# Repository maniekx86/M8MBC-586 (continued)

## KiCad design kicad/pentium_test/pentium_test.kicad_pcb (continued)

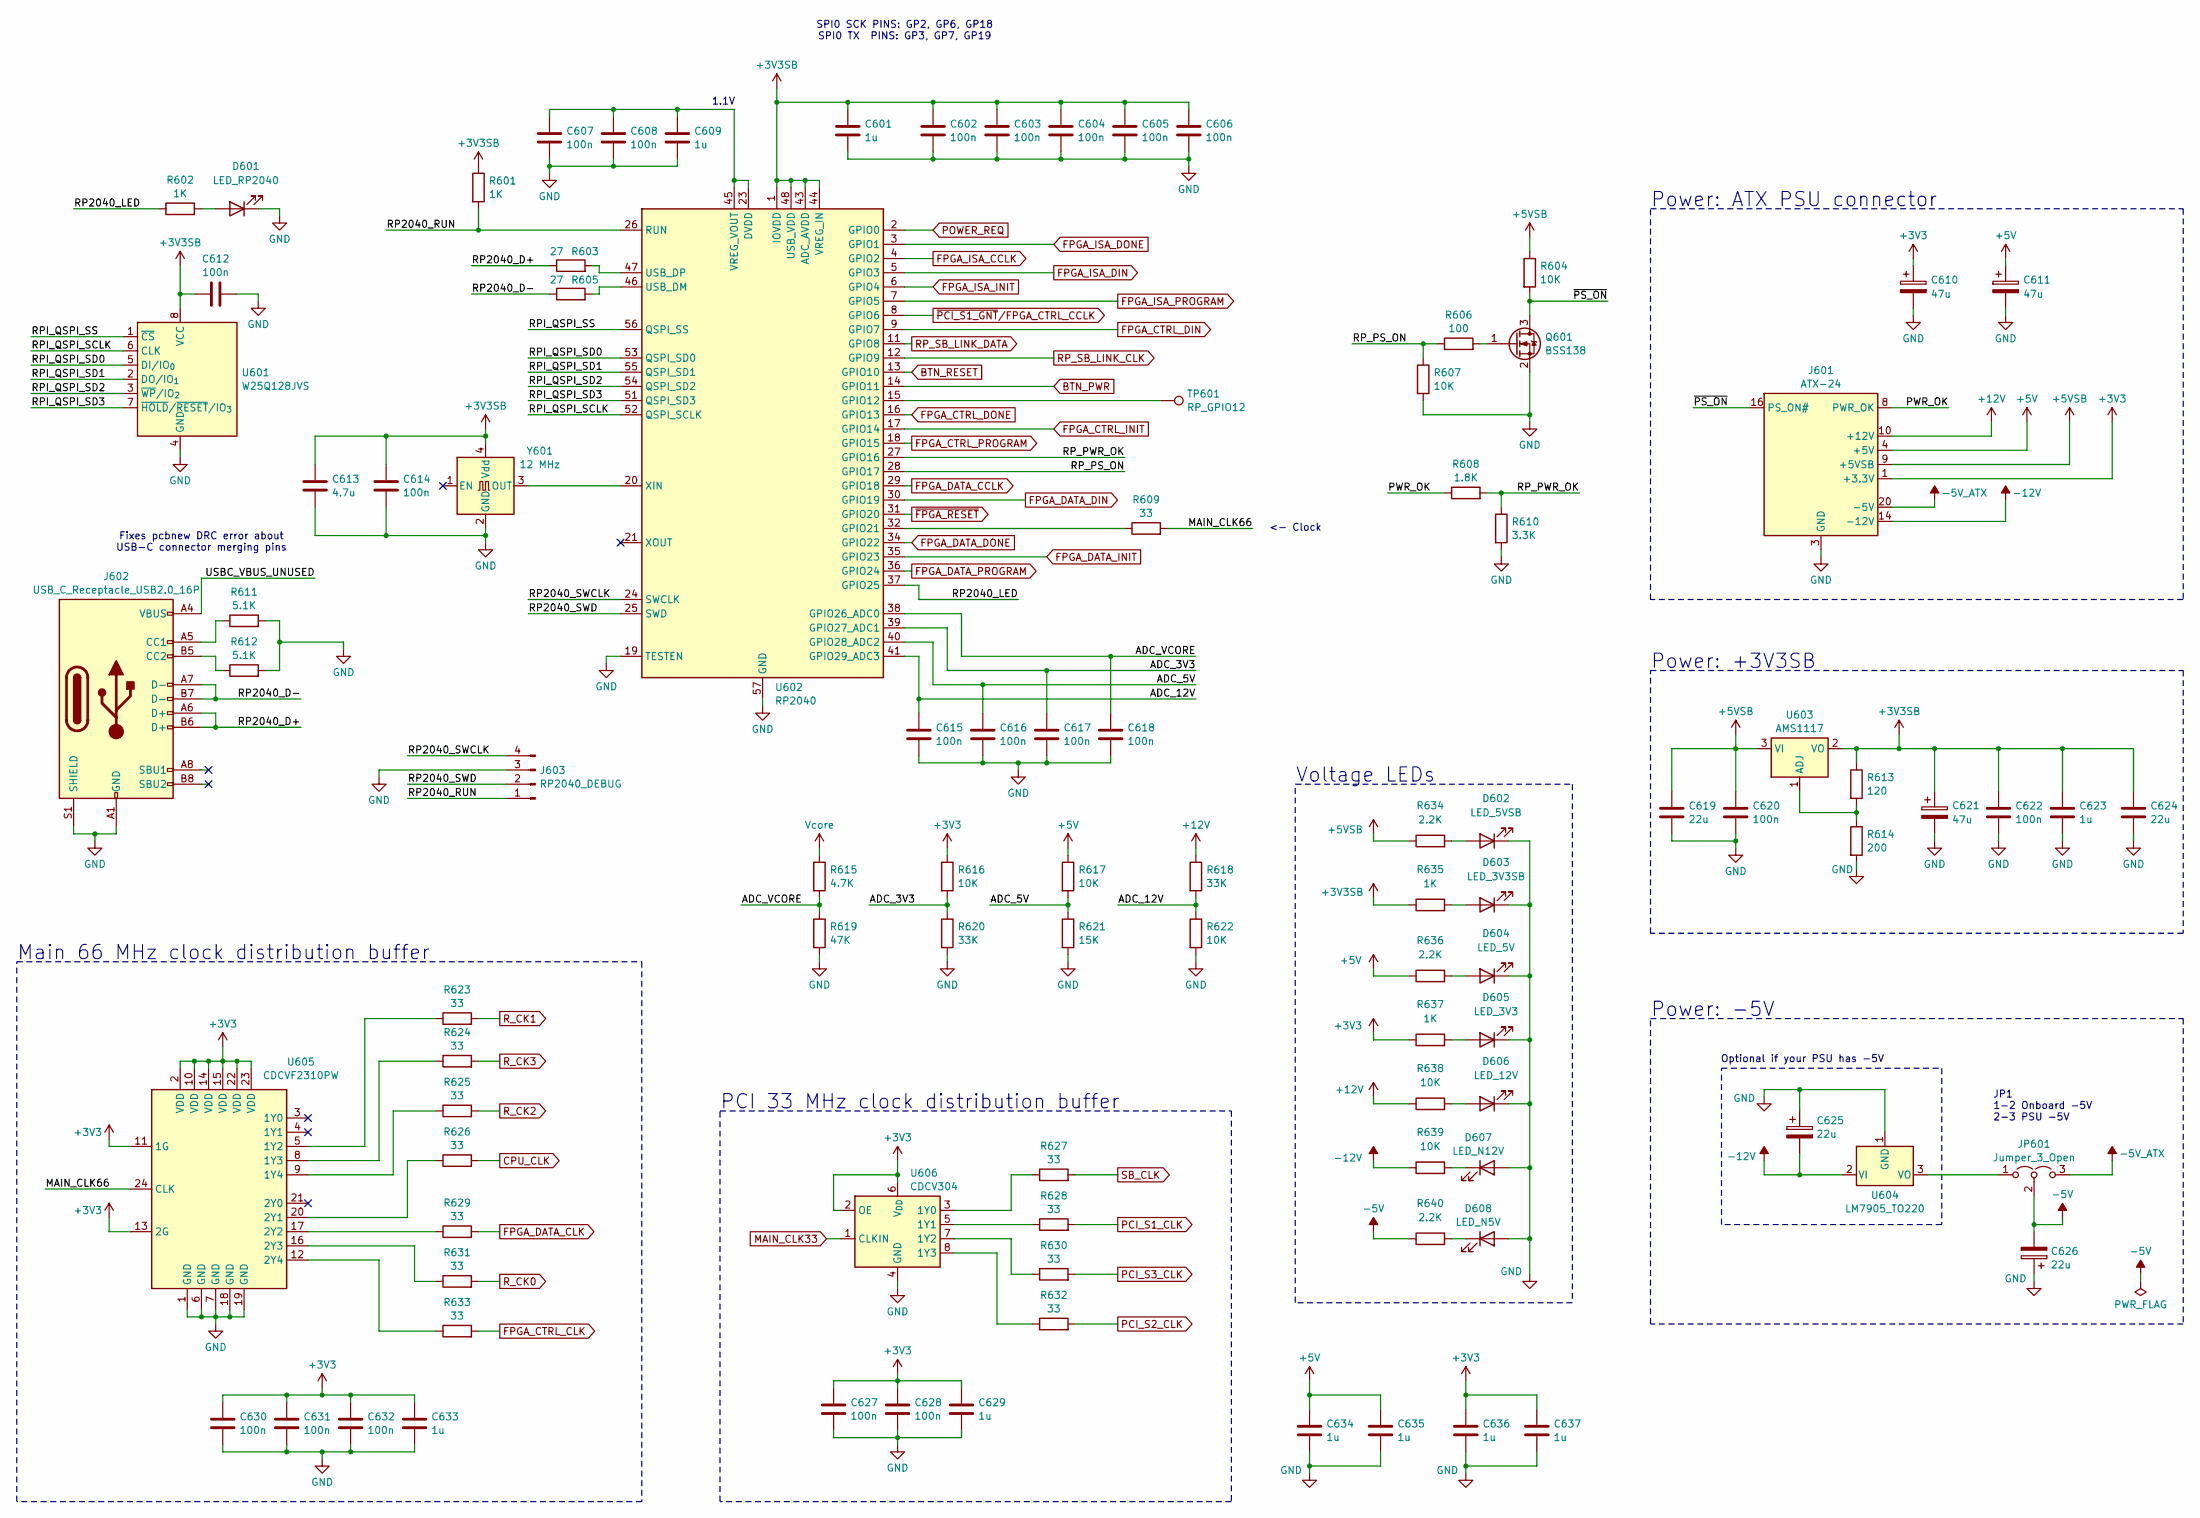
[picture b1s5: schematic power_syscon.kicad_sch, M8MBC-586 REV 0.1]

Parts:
C601, C609, C623, C629, C633, C634, C635, C636, C637: 1u; C_0805_2012Metric
C602, C603, C604, C605, C606, C607, C608, C612, C614, C615, C616, C617, C618, C620, C622, C627, C628, C630, C631, C632: 100n; C_0603_1608Metric
C610, C611, C621: 47u; CP_Radial_D5.0mm_P2.50mm
C613: 4.7u; C_0603_1608Metric
C619, C624: 22u; C_1206_3216Metric
C625, C626: 22u; CP_Radial_D5.0mm_P2.50mm
D601: LED_RP2040; LED_0603_1608Metric
D602: LED_5VSB; LED_0603_1608Metric
D603: LED_3V3SB; LED_0603_1608Metric
D604: LED_5V; LED_0603_1608Metric
D605: LED_3V3; LED_0603_1608Metric
D606: LED_12V; LED_0603_1608Metric
D607: LED_N12V; LED_0603_1608Metric
D608: LED_N5V; LED_0603_1608Metric
J601: ATX-24; Molex_Mini-Fit_Jr_5566-24A2_2x12_P4.20mm_Vertical
J602: USB_C_Receptacle_USB2.0_16P; USB_C_Receptacle_HRO_TYPE-C-31-M-12
J603: RP2040_DEBUG; PinHeader_1x04_P2.54mm_Vertical
JP601: Jumper_3_Open; PinHeader_1x03_P2.54mm_Vertical
Q601: BSS138; SOT-23
R601, R602, R635, R637: 1K; R_0603_1608Metric
R603, R605: 27; R_0603_1608Metric
R604, R607, R616, R617, R622, R638, R639: 10K; R_0603_1608Metric
R606: 100; R_0603_1608Metric
R608: 1.8K; R_0603_1608Metric
R609, R623, R624, R625, R626, R627, R628, R629, R630, R631, R632, R633: 33; R_0603_1608Metric
R610: 3.3K; R_0603_1608Metric
R611, R612: 5.1K; R_0603_1608Metric
R613: 120; R_0603_1608Metric
R614: 200; R_0603_1608Metric
R615: 4.7K; R_0603_1608Metric
R618, R620: 33K; R_0603_1608Metric
R619: 47K; R_0603_1608Metric
R621: 15K; R_0603_1608Metric
R634, R636, R640: 2.2K; R_0603_1608Metric
TP601: RP_GPIO12; TestPoint_Pad_D1.0mm
U601: W25Q128JVS; SOIC-8_5.3x5.3mm_P1.27mm
U602: RP2040; QFN-56-1EP_7x7mm_P0.4mm_EP3.2x3.2mm
U603: AMS1117; SOT-223-3_TabPin2
U604: LM7905_TO220; TO-220-3_Vertical
U605: CDCVF2310PW; TSSOP-24_4.4x7.8mm_P0.65mm
U606: CDCV304; TSSOP-8_4.4x3mm_P0.65mm
Y601: 12 MHz; Crystal_SMD_7050-4Pin_7.0x5.0mm

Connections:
+3V3: C610.1, C627.1, C628.1, C629.1, C630.1, C631.1, C632.1, C633.1, C636.1, C637.1, J601.1 (+3.3V), J601.2 (+3.3V), J601.12 (+3.3V), J601.13 (+3.3V), R616.1, R637.1, U605.2 (VDD), U605.10 (VDD), U605.11 (1G), U605.13 (2G), U605.14 (VDD), U605.15 (VDD), U605.22 (VDD), U605.23 (VDD), U606.2 (OE), U606.6 (V_{DD}); also elsewhere on the board
+3V3SB: C601.1, C602.1, C603.1, C604.1, C605.1, C606.1, C612.1, C613.1, C614.1, C621.1, C622.1, C623.1, C624.1, R601.1, R613.1, R635.1, U601.8 (VCC), U602.1 (IOVDD), U602.10 (IOVDD), U602.22 (IOVDD), U602.33 (IOVDD), U602.42 (IOVDD), U602.43 (ADC_AVDD), U602.44 (VREG_IN), U602.48 (USB_VDD), U602.49 (IOVDD), U603.2 (VO), Y601.4 (Vdd); also elsewhere on the board
+5V: C611.1, C634.1, C635.1, J601.4 (+5V), J601.6 (+5V), J601.21 (+5V), J601.22 (+5V), J601.23 (+5V), R617.1, R636.1; also elsewhere on the board
+5VSB: C619.1, C620.1, J601.9 (+5VSB), R604.1, R634.1, U603.3 (VI)
+12V: J601.10 (+12V), J601.11 (+12V), R618.1, R638.1; also elsewhere on the board
-5V: C626.2, JP601.2 (C), R640.1; also elsewhere on the board
-5V_ATX: J601.20 (-5V), JP601.3 (B)
-12V: C625.2, J601.14 (-12V), R639.1, U604.2 (VI); also elsewhere on the board
/power_syscon/ADC_3V3: C617.1, R616.2, R620.1, U602.39 (GPIO27_ADC1)
/power_syscon/ADC_5V: C616.1, R617.2, R621.1, U602.40 (GPIO28_ADC2)
/power_syscon/ADC_12V: C615.1, R618.2, R622.1, U602.41 (GPIO29_ADC3)
/power_syscon/ADC_VCORE: C618.1, R615.2, R619.1, U602.38 (GPIO26_ADC0)
/power_syscon/MAIN_CLK66: R609.2, U605.24 (CLK)
/power_syscon/PWR_OK: J601.8 (PWR_OK), R608.1
/power_syscon/RP2040_D+: J602.A6 (D+), J602.B6 (D+), R603.1
/power_syscon/RP2040_D-: J602.A7 (D-), J602.B7 (D-), R605.1
/power_syscon/RP2040_LED: R602.1, U602.37 (GPIO25)
/power_syscon/RP2040_RUN: J603.1, R601.2, U602.26 (RUN)
/power_syscon/RP2040_SWCLK: J603.4, U602.24 (SWCLK)
/power_syscon/RP2040_SWD: J603.2, U602.25 (SWD)
/power_syscon/RPI_QSPI_SCLK: U601.6 (CLK), U602.52 (QSPI_SCLK)
/power_syscon/RPI_QSPI_SD0: U601.5 (DI/IO_{0}), U602.53 (QSPI_SD0)
/power_syscon/RPI_QSPI_SD1: U601.2 (DO/IO_{1}), U602.55 (QSPI_SD1)
/power_syscon/RPI_QSPI_SD2: U601.3 (~WP/IO_{2}), U602.54 (QSPI_SD2)
/power_syscon/RPI_QSPI_SD3: U601.7 (~HOLD/~RESET/IO_{3}), U602.51 (QSPI_SD3)
/power_syscon/RPI_QSPI_SS: U601.1 (~CS), U602.56 (QSPI_SS)
/power_syscon/RP_PS_ON: R606.1, R607.1, U602.28 (GPIO17)
/power_syscon/RP_PWR_OK: R608.2, R610.1, U602.27 (GPIO16)
/power_syscon/USBC_VBUS_UNUSED: J602.A4 (VBUS), J602.A9 (VBUS), J602.B4 (VBUS), J602.B9 (VBUS)
/power_syscon/~PS_ON: J601.16 (PS_ON#), Q601.3 (D), R604.2
BTN_PWR: U602.14 (GPIO11); also elsewhere on the board
BTN_RESET: U602.13 (GPIO10); also elsewhere on the board
CPU_CLK: R626.2; also elsewhere on the board
FPGA_CTRL_CLK: R633.2; also elsewhere on the board
FPGA_CTRL_DIN: U602.9 (GPIO7); also elsewhere on the board
FPGA_CTRL_DONE: U602.16 (GPIO13); also elsewhere on the board
FPGA_CTRL_INIT: U602.17 (GPIO14); also elsewhere on the board
FPGA_CTRL_PROGRAM: U602.18 (GPIO15); also elsewhere on the board
FPGA_DATA_CCLK: U602.29 (GPIO18); also elsewhere on the board
FPGA_DATA_CLK: R629.2; also elsewhere on the board
FPGA_DATA_DIN: U602.30 (GPIO19); also elsewhere on the board
FPGA_DATA_DONE: U602.34 (GPIO22); also elsewhere on the board
FPGA_DATA_INIT: U602.35 (GPIO23); also elsewhere on the board
FPGA_DATA_PROGRAM: U602.36 (GPIO24); also elsewhere on the board
FPGA_ISA_CCLK: U602.4 (GPIO2); also elsewhere on the board
FPGA_ISA_DIN: U602.5 (GPIO3); also elsewhere on the board
FPGA_ISA_DONE: U602.3 (GPIO1); also elsewhere on the board
FPGA_ISA_INIT: U602.6 (GPIO4); also elsewhere on the board
FPGA_ISA_PROGRAM: U602.7 (GPIO5); also elsewhere on the board
GND: C601.2, C602.2, C603.2, C604.2, C605.2, C606.2, C607.2, C608.2, C609.2, C610.2, C611.2, C612.2, C613.2, C614.2, C615.2, C616.2, C617.2, C618.2, C619.2, C620.2, C621.2, C622.2, C623.2, C624.2, C625.1, C626.1, C627.2, C628.2, C629.2, C630.2, C631.2, C632.2, C633.2, C634.2, C635.2, C636.2, C637.2, D601.1 (K), D602.1 (K), D603.1 (K), D604.1 (K), D605.1 (K), D606.1 (K), D607.2 (A), D608.2 (A), J601.3 (GND), J601.5 (GND), J601.7 (GND), J601.15 (GND), J601.17 (GND), J601.18 (GND), J601.19 (GND), J601.24 (GND), J602.A1 (GND), J602.A12 (GND), J602.B1 (GND), J602.B12 (GND), J602.S1 (SHIELD), J603.3, Q601.2 (S), R607.2, R610.2, R611.2, R612.2, R614.2, R619.2, R620.2, R621.2, R622.2, U601.4 (GND), U602.19 (TESTEN), U602.57 (GND), U604.1 (GND), U605.1 (GND), U605.6 (GND), U605.7 (GND), U605.18 (GND), U605.19 (GND), U606.4 (GND), Y601.2 (GND); also elsewhere on the board
MAIN_CLK33: U606.1 (CLKIN); also elsewhere on the board
unnamed: D601.2 (A), R602.2
unnamed: D602.2 (A), R634.2
unnamed: D603.2 (A), R635.2
unnamed: D604.2 (A), R636.2
unnamed: D605.2 (A), R637.2
unnamed: D606.2 (A), R638.2
unnamed: D607.1 (K), R639.2
unnamed: D608.1 (K), R640.2
unnamed: J602.A5 (CC1), R611.1
unnamed: J602.B5 (CC2), R612.1
unnamed: JP601.1 (A), U604.3 (VO)
unnamed: Q601.1 (G), R606.2
unnamed: TP601.1, U602.15 (GPIO12)
unnamed: R609.1, U602.32 (GPIO21)
unnamed: R605.2, U602.46 (USB_DM)
unnamed: R603.2, U602.47 (USB_DP)
unnamed: C607.1, C608.1, C609.1, U602.23 (DVDD), U602.45 (VREG_VOUT), U602.50 (DVDD)
unnamed: U602.20 (XIN), Y601.3 (OUT)
unnamed: R613.2, R614.1, U603.1 (ADJ)
unnamed: R623.1, U605.5 (1Y2)
unnamed: R624.1, U605.8 (1Y3)
unnamed: R625.1, U605.9 (1Y4)
unnamed: R626.1, U605.20 (2Y1)
unnamed: R629.1, U605.17 (2Y2)
unnamed: R631.1, U605.16 (2Y3)
unnamed: R633.1, U605.12 (2Y4)
unnamed: R627.1, U606.3 (1Y0)
unnamed: R628.1, U606.5 (1Y1)
unnamed: R630.1, U606.7 (1Y2)
unnamed: R632.1, U606.8 (1Y3)
PCI_S1_CLK: R628.2; also elsewhere on the board
PCI_S2_CLK: R632.2; also elsewhere on the board
PCI_S3_CLK: R630.2; also elsewhere on the board
POWER_REQ: U602.2 (GPIO0); also elsewhere on the board
RP_SB_LINK_CLK: U602.12 (GPIO9); also elsewhere on the board
RP_SB_LINK_DATA: U602.11 (GPIO8); also elsewhere on the board
R_CK0: R631.2; also elsewhere on the board
R_CK1: R623.2; also elsewhere on the board
R_CK2: R625.2; also elsewhere on the board
R_CK3: R624.2; also elsewhere on the board
SB_CLK: R627.2; also elsewhere on the board
Vcore: R615.1; also elsewhere on the board
~FPGA_RESET: U602.31 (GPIO20); also elsewhere on the board
~PCI_S1_GNT/FPGA_CTRL_CCLK: U602.8 (GPIO6); also elsewhere on the board

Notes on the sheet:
PCI 33 MHz clock distribution buffer
Fixes pcbnew DRC error about USB-C connector merging pins
JP1 1-2 Onboard -5V 2-3 PSU -5V
Power: +3V3SB
SPI0 SCK PINS: GP2, GP6, GP18 SPI0 TX PINS: GP3, GP7, GP19
1.1V
Voltage LEDs
<- Clock
Optional if your PSU has -5V
Power: -5V
Power: ATX PSU connector
Main 66 MHz clock distribution buffer

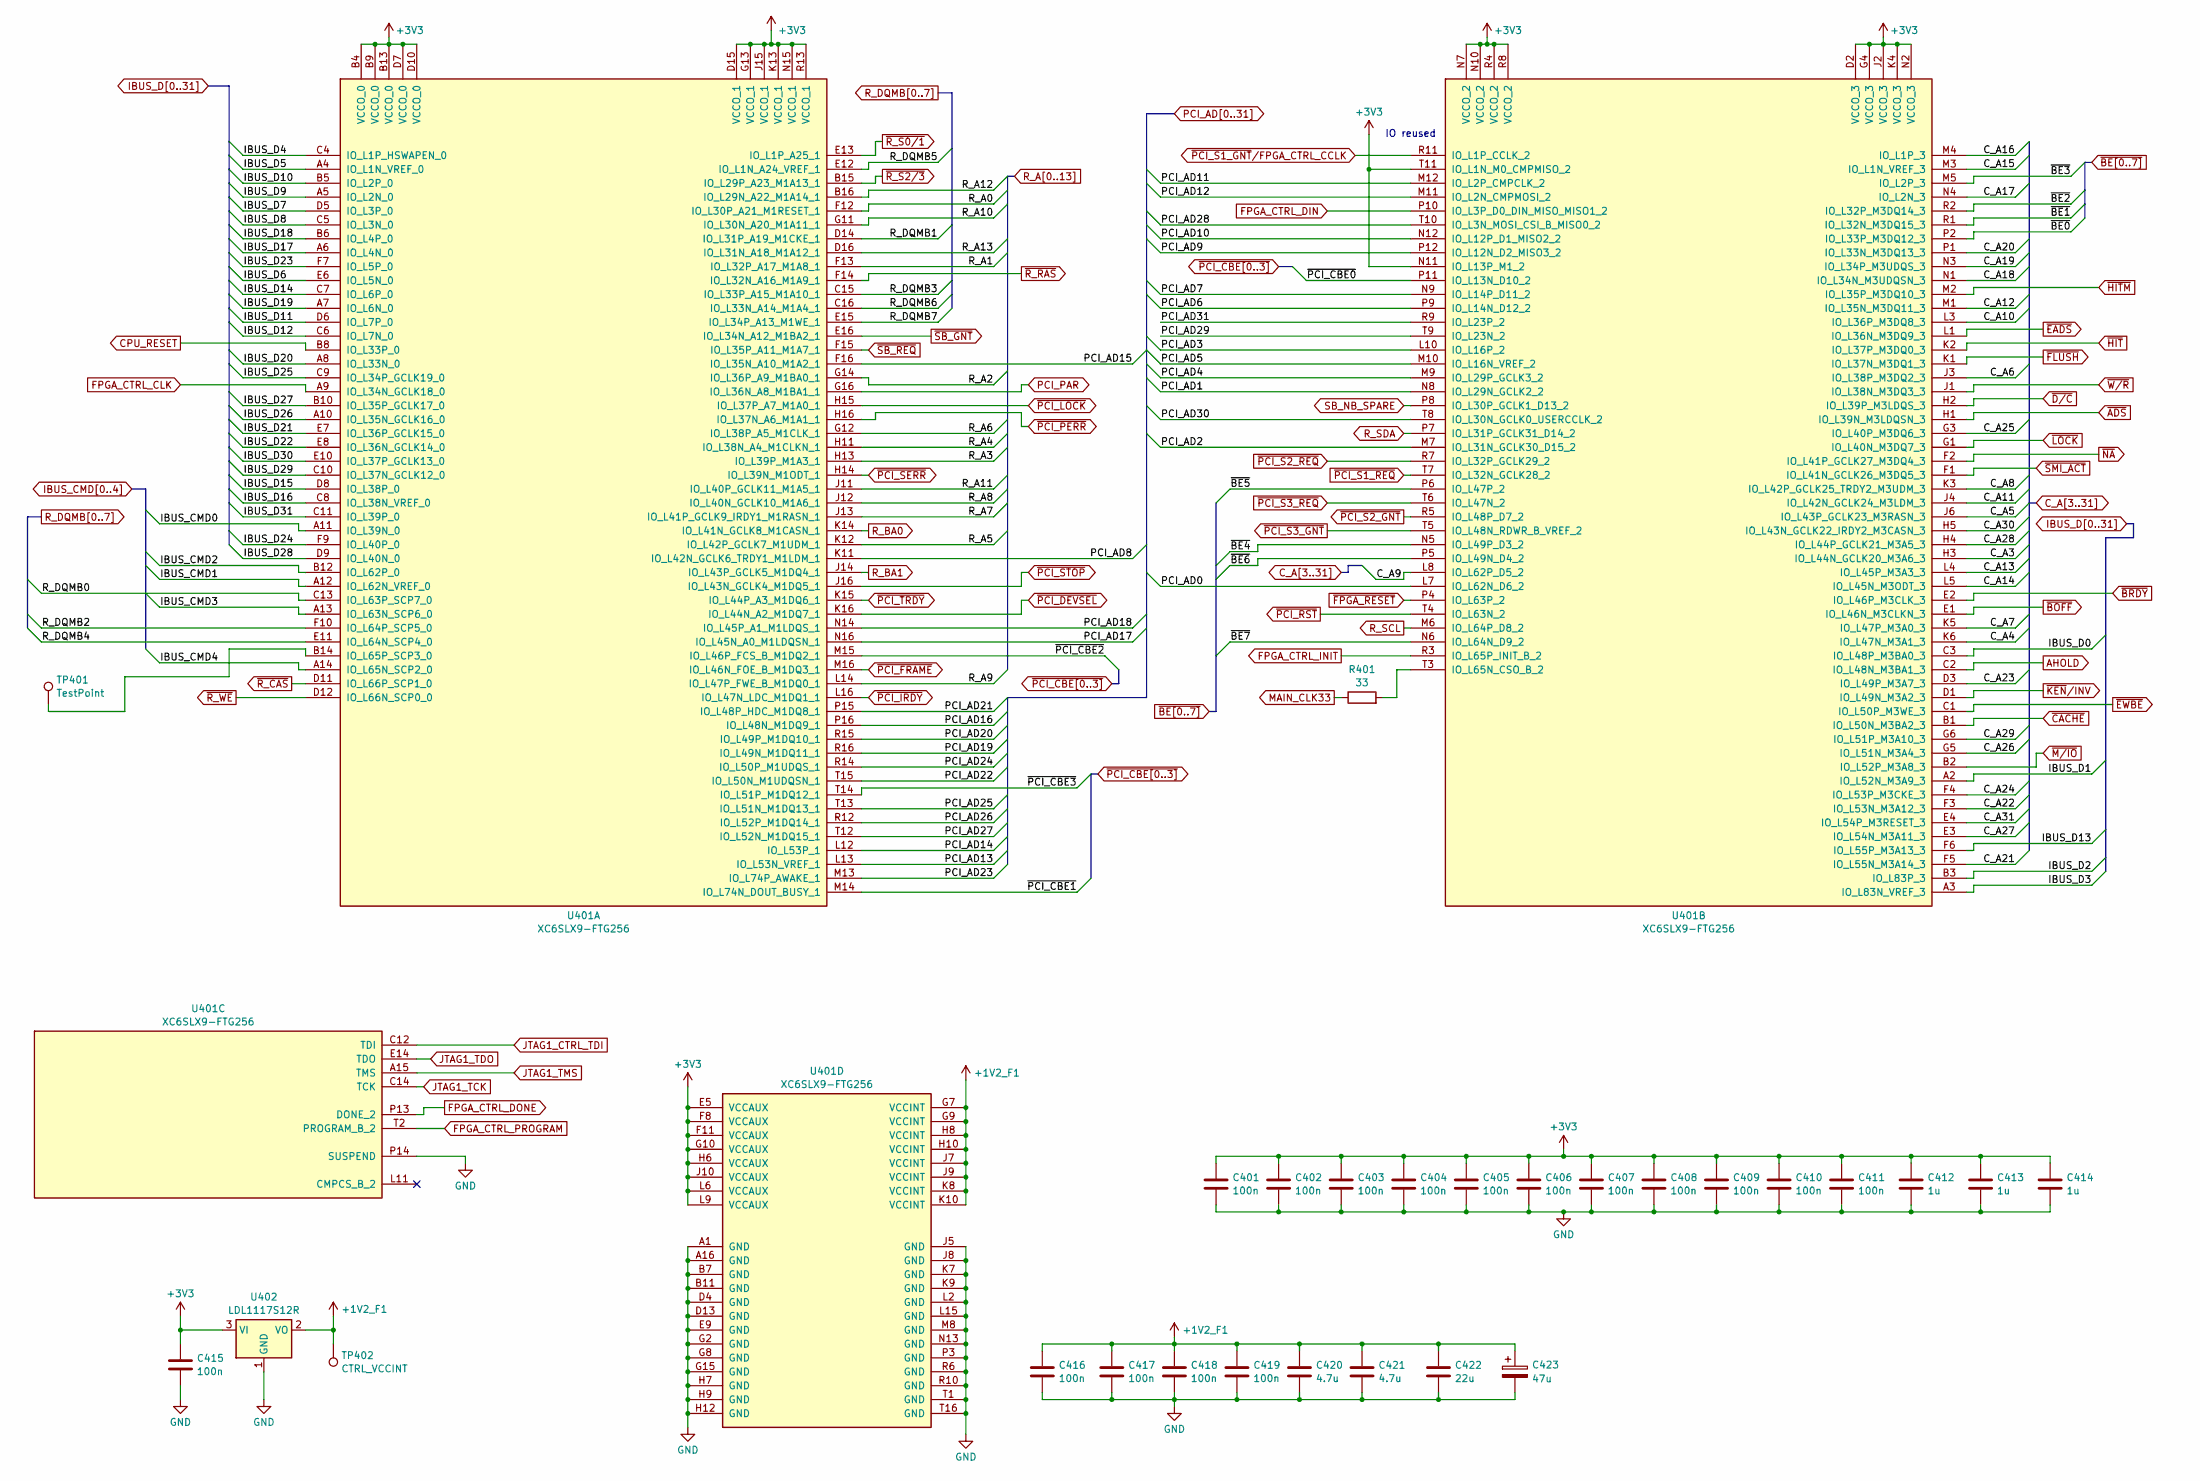
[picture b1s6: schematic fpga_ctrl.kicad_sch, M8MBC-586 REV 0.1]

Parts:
C401, C402, C403, C404, C405, C406, C407, C408, C409, C410, C411, C415, C416, C417, C418, C419: 100n; C_0603_1608Metric
C412, C413, C414: 1u; C_0805_2012Metric
C420, C421: 4.7u; C_0603_1608Metric
C422: 22u; C_1206_3216Metric
C423: 47u; CP_Radial_D5.0mm_P2.50mm
R401: 33; R_0603_1608Metric
TP401: TestPoint; TestPoint_Pad_D1.0mm
TP402: CTRL_VCCINT; TestPoint_Pad_D1.0mm
U401: XC6SLX9-FTG256; Xilinx_FTG256
U402: LDL1117S12R; SOT-223-3_TabPin2

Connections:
+1V2_F1: C416.1, C417.1, C418.1, C419.1, C420.1, C421.1, C422.1, C423.1, TP402.1, U401.G7 (VCCINT), U401.G9 (VCCINT), U401.H8 (VCCINT), U401.H10 (VCCINT), U401.J7 (VCCINT), U401.J9 (VCCINT), U401.K8 (VCCINT), U401.K10 (VCCINT), U402.2 (VO)
+3V3: C401.1, C402.1, C403.1, C404.1, C405.1, C406.1, C407.1, C408.1, C409.1, C410.1, C411.1, C412.1, C413.1, C414.1, C415.1, U401.B4 (VCCO_0), U401.B9 (VCCO_0), U401.B13 (VCCO_0), U401.D2 (VCCO_3), U401.D7 (VCCO_0), U401.D10 (VCCO_0), U401.D15 (VCCO_1), U401.E5 (VCCAUX), U401.F8 (VCCAUX), U401.F11 (VCCAUX), U401.G4 (VCCO_3), U401.G10 (VCCAUX), U401.G13 (VCCO_1), U401.H6 (VCCAUX), U401.J2 (VCCO_3), U401.J10 (VCCAUX), U401.J15 (VCCO_1), U401.K4 (VCCO_3), U401.K13 (VCCO_1), U401.L6 (VCCAUX), U401.L9 (VCCAUX), U401.N2 (VCCO_3), U401.N7 (VCCO_2), U401.N10 (VCCO_2), U401.N11 (IO_L13P_M1_2), U401.N15 (VCCO_1), U401.R4 (VCCO_2), U401.R8 (VCCO_2), U401.R13 (VCCO_1), U401.T11 (IO_L1N_M0_CMPMISO_2), U402.3 (VI); also elsewhere on the board
AHOLD: U401.C2 (IO_L48N_M3BA1_3); also elsewhere on the board
CPU_RESET: U401.B8 (IO_L33P_0); also elsewhere on the board
C_A3: U401.H3 (IO_L44N_GCLK20_M3A6_3); also elsewhere on the board
C_A4: U401.K6 (IO_L47N_M3A1_3); also elsewhere on the board
C_A5: U401.J6 (IO_L43P_GCLK23_M3RASN_3); also elsewhere on the board
C_A6: U401.J3 (IO_L38P_M3DQ2_3); also elsewhere on the board
C_A7: U401.K5 (IO_L47P_M3A0_3); also elsewhere on the board
C_A8: U401.K3 (IO_L42P_GCLK25_TRDY2_M3UDM_3); also elsewhere on the board
C_A9: U401.L8 (IO_L62P_D5_2); also elsewhere on the board
C_A10: U401.L3 (IO_L36P_M3DQ8_3); also elsewhere on the board
C_A11: U401.J4 (IO_L42N_GCLK24_M3LDM_3); also elsewhere on the board
C_A12: U401.M1 (IO_L35N_M3DQ11_3); also elsewhere on the board
C_A13: U401.L4 (IO_L45P_M3A3_3); also elsewhere on the board
C_A14: U401.L5 (IO_L45N_M3ODT_3); also elsewhere on the board
C_A15: U401.M3 (IO_L1N_VREF_3); also elsewhere on the board
C_A16: U401.M4 (IO_L1P_3); also elsewhere on the board
C_A17: U401.N4 (IO_L2N_3); also elsewhere on the board
C_A18: U401.N1 (IO_L34N_M3UDQSN_3); also elsewhere on the board
C_A19: U401.N3 (IO_L34P_M3UDQS_3); also elsewhere on the board
C_A20: U401.P1 (IO_L33N_M3DQ13_3); also elsewhere on the board
C_A21: U401.F5 (IO_L55N_M3A14_3); also elsewhere on the board
C_A22: U401.F3 (IO_L53N_M3A12_3); also elsewhere on the board
C_A23: U401.D3 (IO_L49P_M3A7_3); also elsewhere on the board
C_A24: U401.F4 (IO_L53P_M3CKE_3); also elsewhere on the board
C_A25: U401.G3 (IO_L40P_M3DQ6_3); also elsewhere on the board
C_A26: U401.G5 (IO_L51N_M3A4_3); also elsewhere on the board
C_A27: U401.E3 (IO_L54N_M3A11_3); also elsewhere on the board
C_A28: U401.H4 (IO_L44P_GCLK21_M3A5_3); also elsewhere on the board
C_A29: U401.G6 (IO_L51P_M3A10_3); also elsewhere on the board
C_A30: U401.H5 (IO_L43N_GCLK22_IRDY2_M3CASN_3); also elsewhere on the board
C_A31: U401.E4 (IO_L54P_M3RESET_3); also elsewhere on the board
FPGA_CTRL_CLK: U401.A9 (IO_L34N_GCLK18_0); also elsewhere on the board
FPGA_CTRL_DIN: U401.P10 (IO_L3P_D0_DIN_MISO_MISO1_2); also elsewhere on the board
FPGA_CTRL_DONE: U401.P13 (DONE_2); also elsewhere on the board
FPGA_CTRL_INIT: U401.R3 (IO_L65P_INIT_B_2); also elsewhere on the board
FPGA_CTRL_PROGRAM: U401.T2 (PROGRAM_B_2); also elsewhere on the board
GND: C401.2, C402.2, C403.2, C404.2, C405.2, C406.2, C407.2, C408.2, C409.2, C410.2, C411.2, C412.2, C413.2, C414.2, C415.2, C416.2, C417.2, C418.2, C419.2, C420.2, C421.2, C422.2, C423.2, U401.A1 (GND), U401.A16 (GND), U401.B7 (GND), U401.B11 (GND), U401.D4 (GND), U401.D13 (GND), U401.E9 (GND), U401.G2 (GND), U401.G8 (GND), U401.G15 (GND), U401.H7 (GND), U401.H9 (GND), U401.H12 (GND), U401.J5 (GND), U401.J8 (GND), U401.K7 (GND), U401.K9 (GND), U401.L2 (GND), U401.L15 (GND), U401.M8 (GND), U401.N13 (GND), U401.P3 (GND), U401.P14 (SUSPEND), U401.R6 (GND), U401.R10 (GND), U401.T1 (GND), U401.T16 (GND), U402.1 (GND); also elsewhere on the board
IBUS_CMD0: U401.A11 (IO_L39N_0); also elsewhere on the board
IBUS_CMD1: U401.A12 (IO_L62N_VREF_0); also elsewhere on the board
IBUS_CMD2: U401.B12 (IO_L62P_0); also elsewhere on the board
IBUS_CMD3: U401.A13 (IO_L63N_SCP6_0); also elsewhere on the board
IBUS_CMD4: U401.A14 (IO_L65N_SCP2_0); also elsewhere on the board
IBUS_D0: U401.C3 (IO_L48P_M3BA0_3); also elsewhere on the board
IBUS_D1: U401.A2 (IO_L52N_M3A9_3); also elsewhere on the board
IBUS_D2: U401.B3 (IO_L83P_3); also elsewhere on the board
IBUS_D3: U401.A3 (IO_L83N_VREF_3); also elsewhere on the board
IBUS_D4: U401.C4 (IO_L1P_HSWAPEN_0); also elsewhere on the board
IBUS_D5: U401.A4 (IO_L1N_VREF_0); also elsewhere on the board
IBUS_D6: U401.E6 (IO_L5N_0); also elsewhere on the board
IBUS_D7: U401.D5 (IO_L3P_0); also elsewhere on the board
IBUS_D8: U401.C5 (IO_L3N_0); also elsewhere on the board
IBUS_D9: U401.A5 (IO_L2N_0); also elsewhere on the board
IBUS_D10: U401.B5 (IO_L2P_0); also elsewhere on the board
IBUS_D11: U401.D6 (IO_L7P_0); also elsewhere on the board
IBUS_D12: U401.C6 (IO_L7N_0); also elsewhere on the board
IBUS_D13: U401.F6 (IO_L55P_M3A13_3); also elsewhere on the board
IBUS_D14: U401.C7 (IO_L6P_0); also elsewhere on the board
IBUS_D15: U401.D8 (IO_L38P_0); also elsewhere on the board
IBUS_D16: U401.C8 (IO_L38N_VREF_0); also elsewhere on the board
IBUS_D17: U401.A6 (IO_L4N_0); also elsewhere on the board
IBUS_D18: U401.B6 (IO_L4P_0); also elsewhere on the board
IBUS_D19: U401.A7 (IO_L6N_0); also elsewhere on the board
IBUS_D20: U401.A8 (IO_L33N_0); also elsewhere on the board
IBUS_D21: U401.E7 (IO_L36P_GCLK15_0); also elsewhere on the board
IBUS_D22: U401.E8 (IO_L36N_GCLK14_0); also elsewhere on the board
IBUS_D23: U401.F7 (IO_L5P_0); also elsewhere on the board
IBUS_D24: U401.F9 (IO_L40P_0); also elsewhere on the board
IBUS_D25: U401.C9 (IO_L34P_GCLK19_0); also elsewhere on the board
IBUS_D26: U401.A10 (IO_L35N_GCLK16_0); also elsewhere on the board
IBUS_D27: U401.B10 (IO_L35P_GCLK17_0); also elsewhere on the board
IBUS_D28: U401.D9 (IO_L40N_0); also elsewhere on the board
IBUS_D29: U401.C10 (IO_L37N_GCLK12_0); also elsewhere on the board
IBUS_D30: U401.E10 (IO_L37P_GCLK13_0); also elsewhere on the board
IBUS_D31: U401.C11 (IO_L39P_0); also elsewhere on the board
JTAG1_CTRL_TDI: U401.C12 (TDI); also elsewhere on the board
JTAG1_TCK: U401.C14 (TCK); also elsewhere on the board
JTAG1_TDO: U401.E14 (TDO); also elsewhere on the board
JTAG1_TMS: U401.A15 (TMS); also elsewhere on the board
MAIN_CLK33: R401.1; also elsewhere on the board
unnamed: TP401.1, U401.B14 (IO_L65P_SCP3_0)
unnamed: R401.2, U401.T3 (IO_L65N_CSO_B_2)
PCI_AD0: U401.L7 (IO_L62N_D6_2); also elsewhere on the board
PCI_AD1: U401.N8 (IO_L29N_GCLK2_2); also elsewhere on the board
PCI_AD2: U401.M7 (IO_L31N_GCLK30_D15_2); also elsewhere on the board
PCI_AD3: U401.L10 (IO_L16P_2); also elsewhere on the board
PCI_AD4: U401.M9 (IO_L29P_GCLK3_2); also elsewhere on the board
PCI_AD5: U401.M10 (IO_L16N_VREF_2); also elsewhere on the board
PCI_AD6: U401.P9 (IO_L14N_D12_2); also elsewhere on the board
PCI_AD7: U401.N9 (IO_L14P_D11_2); also elsewhere on the board
PCI_AD8: U401.K11 (IO_L42N_GCLK6_TRDY1_M1LDM_1); also elsewhere on the board
PCI_AD9: U401.P12 (IO_L12N_D2_MISO3_2); also elsewhere on the board
PCI_AD10: U401.N12 (IO_L12P_D1_MISO2_2); also elsewhere on the board
PCI_AD11: U401.M12 (IO_L2P_CMPCLK_2); also elsewhere on the board
PCI_AD12: U401.M11 (IO_L2N_CMPMOSI_2); also elsewhere on the board
PCI_AD13: U401.L13 (IO_L53N_VREF_1); also elsewhere on the board
PCI_AD14: U401.L12 (IO_L53P_1); also elsewhere on the board
PCI_AD15: U401.F16 (IO_L35N_A10_M1A2_1); also elsewhere on the board
PCI_AD16: U401.P16 (IO_L48N_M1DQ9_1); also elsewhere on the board
PCI_AD17: U401.N16 (IO_L45N_A0_M1LDQSN_1); also elsewhere on the board
PCI_AD18: U401.N14 (IO_L45P_A1_M1LDQS_1); also elsewhere on the board
PCI_AD19: U401.R16 (IO_L49N_M1DQ11_1); also elsewhere on the board
PCI_AD20: U401.R15 (IO_L49P_M1DQ10_1); also elsewhere on the board
PCI_AD21: U401.P15 (IO_L48P_HDC_M1DQ8_1); also elsewhere on the board
PCI_AD22: U401.T15 (IO_L50N_M1UDQSN_1); also elsewhere on the board
PCI_AD23: U401.M13 (IO_L74P_AWAKE_1); also elsewhere on the board
PCI_AD24: U401.R14 (IO_L50P_M1UDQS_1); also elsewhere on the board
PCI_AD25: U401.T13 (IO_L51N_M1DQ13_1); also elsewhere on the board
PCI_AD26: U401.R12 (IO_L52P_M1DQ14_1); also elsewhere on the board
PCI_AD27: U401.T12 (IO_L52N_M1DQ15_1); also elsewhere on the board
PCI_AD28: U401.T10 (IO_L3N_MOSI_CSI_B_MISO0_2); also elsewhere on the board
PCI_AD29: U401.T9 (IO_L23N_2); also elsewhere on the board
PCI_AD30: U401.T8 (IO_L30N_GCLK0_USERCCLK_2); also elsewhere on the board
PCI_AD31: U401.R9 (IO_L23P_2); also elsewhere on the board
PCI_PAR: U401.G16 (IO_L36N_A8_M1BA1_1); also elsewhere on the board
R_A0: U401.F12 (IO_L30P_A21_M1RESET_1); also elsewhere on the board
R_A1: U401.F13 (IO_L32P_A17_M1A8_1); also elsewhere on the board
R_A2: U401.G14 (IO_L36P_A9_M1BA0_1); also elsewhere on the board
R_A3: U401.H13 (IO_L39P_M1A3_1); also elsewhere on the board
R_A4: U401.H11 (IO_L38N_A4_M1CLKN_1); also elsewhere on the board
R_A5: U401.K12 (IO_L42P_GCLK7_M1UDM_1); also elsewhere on the board
R_A6: U401.G12 (IO_L38P_A5_M1CLK_1); also elsewhere on the board
R_A7: U401.J13 (IO_L41P_GCLK9_IRDY1_M1RASN_1); also elsewhere on the board
R_A8: U401.J12 (IO_L40N_GCLK10_M1A6_1); also elsewhere on the board
R_A9: U401.L14 (IO_L47P_FWE_B_M1DQ0_1); also elsewhere on the board
R_A10: U401.G11 (IO_L30N_A20_M1A11_1); also elsewhere on the board
R_A11: U401.J11 (IO_L40P_GCLK11_M1A5_1); also elsewhere on the board
R_A12: U401.B16 (IO_L29N_A22_M1A14_1); also elsewhere on the board
R_A13: U401.D16 (IO_L31N_A18_M1A12_1); also elsewhere on the board
R_BA0: U401.K14 (IO_L41N_GCLK8_M1CASN_1); also elsewhere on the board
R_BA1: U401.J14 (IO_L43P_GCLK5_M1DQ4_1); also elsewhere on the board
R_DQMB0: U401.C13 (IO_L63P_SCP7_0); also elsewhere on the board
R_DQMB1: U401.D14 (IO_L31P_A19_M1CKE_1); also elsewhere on the board
R_DQMB2: U401.F10 (IO_L64P_SCP5_0); also elsewhere on the board
R_DQMB3: U401.C15 (IO_L33P_A15_M1A10_1); also elsewhere on the board
R_DQMB4: U401.E11 (IO_L64N_SCP4_0); also elsewhere on the board
R_DQMB5: U401.E12 (IO_L1N_A24_VREF_1); also elsewhere on the board
R_DQMB6: U401.C16 (IO_L33N_A14_M1A4_1); also elsewhere on the board
R_DQMB7: U401.E15 (IO_L34P_A13_M1WE_1); also elsewhere on the board
R_SCL: U401.M6 (IO_L64P_D8_2); also elsewhere on the board
R_SDA: U401.P7 (IO_L31P_GCLK31_D14_2); also elsewhere on the board
SB_NB_SPARE: U401.P8 (IO_L30P_GCLK1_D13_2); also elsewhere on the board
~ADS: U401.H1 (IO_L39N_M3LDQSN_3); also elsewhere on the board
~BE0: U401.P2 (IO_L33P_M3DQ12_3); also elsewhere on the board
~BE1: U401.R1 (IO_L32N_M3DQ15_3); also elsewhere on the board
~BE2: U401.R2 (IO_L32P_M3DQ14_3); also elsewhere on the board
~BE3: U401.M5 (IO_L2P_3); also elsewhere on the board
~BE4: U401.N5 (IO_L49P_D3_2); also elsewhere on the board
~BE5: U401.P6 (IO_L47P_2); also elsewhere on the board
~BE6: U401.P5 (IO_L49N_D4_2); also elsewhere on the board
~BE7: U401.N6 (IO_L64N_D9_2); also elsewhere on the board
~BOFF: U401.E1 (IO_L46N_M3CLKN_3); also elsewhere on the board
~BRDY: U401.E2 (IO_L46P_M3CLK_3); also elsewhere on the board
~CACHE: U401.B1 (IO_L50N_M3BA2_3); also elsewhere on the board
~D/C: U401.H2 (IO_L39P_M3LDQS_3); also elsewhere on the board
~EADS: U401.L1 (IO_L36N_M3DQ9_3); also elsewhere on the board
~EWBE: U401.C1 (IO_L50P_M3WE_3); also elsewhere on the board
~FLUSH: U401.K1 (IO_L37N_M3DQ1_3); also elsewhere on the board
~FPGA_RESET: U401.P4 (IO_L63P_2); also elsewhere on the board
~HITM: U401.M2 (IO_L35P_M3DQ10_3); also elsewhere on the board
~HIT: U401.K2 (IO_L37P_M3DQ0_3); also elsewhere on the board
~KEN/INV: U401.D1 (IO_L49N_M3A2_3); also elsewhere on the board
~LOCK: U401.G1 (IO_L40N_M3DQ7_3); also elsewhere on the board
~M/IO: U401.B2 (IO_L52P_M3A8_3); also elsewhere on the board
~NA: U401.F2 (IO_L41P_GCLK27_M3DQ4_3); also elsewhere on the board
~PCI_CBE0: U401.P11 (IO_L13N_D10_2); also elsewhere on the board
~PCI_CBE1: U401.M14 (IO_L74N_DOUT_BUSY_1); also elsewhere on the board
~PCI_CBE2: U401.M15 (IO_L46P_FCS_B_M1DQ2_1); also elsewhere on the board
~PCI_CBE3: U401.T14 (IO_L51P_M1DQ12_1); also elsewhere on the board
~PCI_DEVSEL: U401.K16 (IO_L44N_A2_M1DQ7_1); also elsewhere on the board
~PCI_FRAME: U401.M16 (IO_L46N_FOE_B_M1DQ3_1); also elsewhere on the board
~PCI_IRDY: U401.L16 (IO_L47N_LDC_M1DQ1_1); also elsewhere on the board
~PCI_LOCK: U401.H15 (IO_L37P_A7_M1A0_1); also elsewhere on the board
~PCI_PERR: U401.H16 (IO_L37N_A6_M1A1_1); also elsewhere on the board
~PCI_RST: U401.T4 (IO_L63N_2); also elsewhere on the board
~PCI_S1_GNT/FPGA_CTRL_CCLK: U401.R11 (IO_L1P_CCLK_2); also elsewhere on the board
~PCI_S1_REQ: U401.T7 (IO_L32N_GCLK28_2); also elsewhere on the board
~PCI_S2_GNT: U401.R5 (IO_L48P_D7_2); also elsewhere on the board
~PCI_S2_REQ: U401.R7 (IO_L32P_GCLK29_2); also elsewhere on the board
~PCI_S3_GNT: U401.T5 (IO_L48N_RDWR_B_VREF_2); also elsewhere on the board
~PCI_S3_REQ: U401.T6 (IO_L47N_2); also elsewhere on the board
~PCI_SERR: U401.H14 (IO_L39N_M1ODT_1); also elsewhere on the board
~PCI_STOP: U401.J16 (IO_L43N_GCLK4_M1DQ5_1); also elsewhere on the board
~PCI_TRDY: U401.K15 (IO_L44P_A3_M1DQ6_1); also elsewhere on the board
~R_CAS: U401.D11 (IO_L66P_SCP1_0); also elsewhere on the board
~R_RAS: U401.F14 (IO_L32N_A16_M1A9_1); also elsewhere on the board
~R_S0/1: U401.E13 (IO_L1P_A25_1); also elsewhere on the board
~R_S2/3: U401.B15 (IO_L29P_A23_M1A13_1); also elsewhere on the board
~R_WE: U401.D12 (IO_L66N_SCP0_0); also elsewhere on the board
~SB_GNT: U401.E16 (IO_L34N_A12_M1BA2_1); also elsewhere on the board
~SB_REQ: U401.F15 (IO_L35P_A11_M1A7_1); also elsewhere on the board
~SMI_ACT: U401.F1 (IO_L41N_GCLK26_M3DQ5_3); also elsewhere on the board
~W/R: U401.J1 (IO_L38N_M3DQ3_3); also elsewhere on the board

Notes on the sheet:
IO reused
